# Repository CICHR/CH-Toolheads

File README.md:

CICHR Toolheads

The changeable toolheads are designed for maximum versatility and seamless integration, communicating directly with the printer via a custom PCB. This PCB enables precise control and coordination between the tool head and the printer, ensuring fast, accurate swaps between different functions. The custom PCB features:

    Heater and High-Power Outputs:
    Two high-power outputs for heaters or PWM-controlled devices with demanding power requirements.

    Temperature Sensing:
    Two thermistor inputs for accurate real-time temperature monitoring.

    PWM Outputs:
    Two PWM outputs for controlling servos, BLTouch sensors, or cooling fans.

    Digital Interfaces:
    One digital input and one digital output for additional functionality, such as endstops or status signaling.

    Stepper Motor Control:
    A dedicated output for driving a single stepper motor, ideal for toolhead-mounted extrusion or positioning tasks.

    Streamlined Communication:
    Ensures reliable communication between the toolhead and the machine, simplifying toolhead management and enhancing modularity.

This system allows you to quickly swap between different toolheads, such as 3D printing extruders, CNC milling tools, lasers, or liquid extruders, without complex rewiring, while maintaining full control over key functions.

Visit our website at www.cichr.com or https://grabcad.com/cichr-1 to learn more about our products, projects, and innovations.

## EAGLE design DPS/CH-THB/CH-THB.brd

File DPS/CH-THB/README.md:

CH-THB: The Versatile Toolhead PCB

The CH-THB is a specialized PCB board designed to manage and control a single toolhead, seamlessly connecting it to the main machine control system. This board is highly versatile, supporting various toolhead types, including 3D printers, lasers, routers, and more.

  Key Features:

      Heater and High-Power Outputs:
        Two high-power outputs for heaters or PWM-controlled devices with demanding power requirements.
      Temperature Sensing:
        Two thermistor inputs for accurate real-time temperature monitoring.
      PWM Outputs:
        Two PWM outputs for controlling servos, BLTouch sensors, or cooling fans.
      Digital Interfaces:
        One digital input and one digital output for additional functionality, such as endstops or status signaling.
      Stepper Motor Control:
        A dedicated output for driving a single stepper motor, ideal for toolhead-mounted extrusion or positioning tasks.
      Streamlined Communication:
        Ensures reliable communication between the toolhead and the machine, simplifying toolhead management and enhancing modularity.

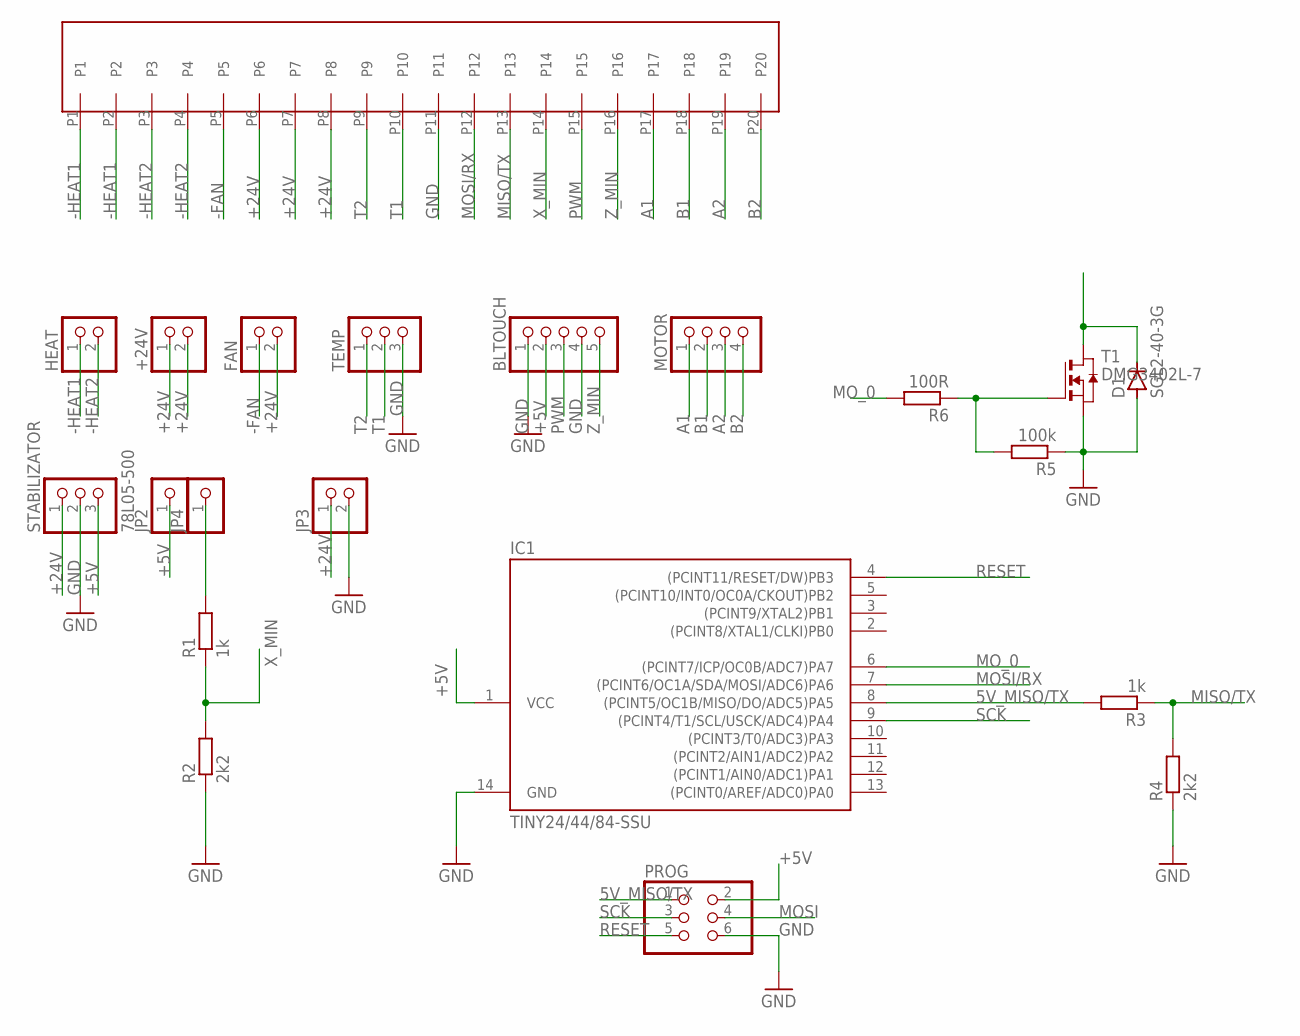
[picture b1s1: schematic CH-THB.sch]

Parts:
+24V: PINHD-1X2/LONG; 1X02
BLTOUCH: PINHD-1X5/LONG; 1X05
D1: SGL2-40-3G; SOD80
FAN: PINHD-1X2/LONG; 1X02
HEAT: PINHD-1X2/LONG; 1X02
IC1: TINY24/44/84-SSU; SOIC14
JP2, JP4: PINHD-1X1/OCT; 1X01/OCT
JP3: PINHD-1X2/OCT; 1X02/OCT
MOTOR: PINHD-1X4/LONG; 1X04
PROG: PINHD-2X3/OCT; 2X03
R1, R3: 1k; R0603
R2, R4: 2k2; R0603
R5: 100k; R0603
R6: 100R; R0603
STABILIZATOR: 78L05-500; 1X03/OCT
T1: DMG3402L-7; SOT-23
TEMP: PINHD-1X3/OCT; 1X03/OCT
U$1: PL20

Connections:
5V_MISO/TX: IC1.8 ((PCINT5/OC1B/MISO/DO/ADC5)PA5), PROG.1, R3.2
+5V: BLTOUCH.2, IC1.1 (VCC), JP2.1, PROG.2, STABILIZATOR.3
+24V: +24V.1, +24V.2, FAN.2, JP3.1, STABILIZATOR.1, U$1.P6, U$1.P7, U$1.P8
-FAN: FAN.1, U$1.P5
-HEAT1: HEAT.1, U$1.P1, U$1.P2
-HEAT2: HEAT.2, U$1.P3, U$1.P4
A1: MOTOR.1, U$1.P17
A2: MOTOR.3, U$1.P19
B1: MOTOR.2, U$1.P18
B2: MOTOR.4, U$1.P20
GND: BLTOUCH.1, BLTOUCH.4, D1.2 (A), IC1.14 (GND), JP3.2, PROG.6, R2.1, R4.1, R5.1, STABILIZATOR.2, T1.2 (S), TEMP.3, U$1.P11
MISO/TX: R3.1, R4.2, U$1.P13
MOSI: PROG.4
MOSI/RX: IC1.7 ((PCINT6/OC1A/SDA/MOSI/ADC6)PA6), U$1.P12
MO_0: IC1.6 ((PCINT7/ICP/OC0B/ADC7)PA7), R6.2
unnamed: JP4.1, R1.2
unnamed: R5.2, R6.1, T1.3 (G)
unnamed: D1.1 (C), T1.1 (D)
PWM: BLTOUCH.3, U$1.P15
RESET: IC1.4 ((PCINT11/RESET/DW)PB3), PROG.5
SCK: IC1.9 ((PCINT4/T1/SCL/USCK/ADC4)PA4), PROG.3
T1: TEMP.2, U$1.P10
T2: TEMP.1, U$1.P9
X_MIN: R1.1, R2.2, U$1.P14
Z_MIN: BLTOUCH.5, U$1.P16

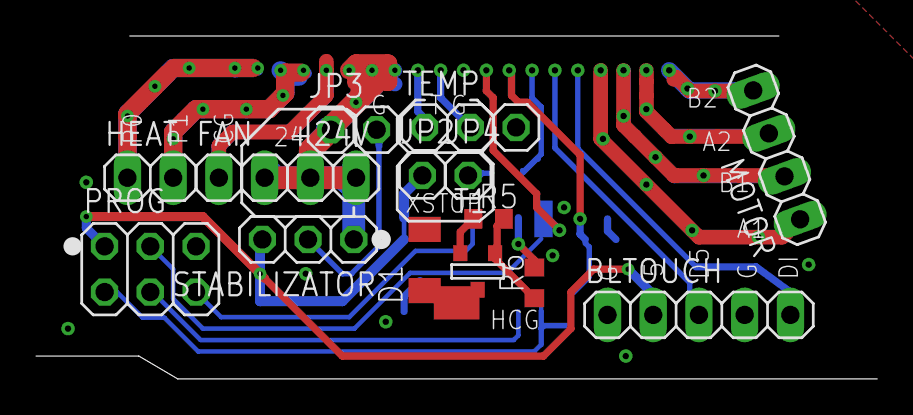
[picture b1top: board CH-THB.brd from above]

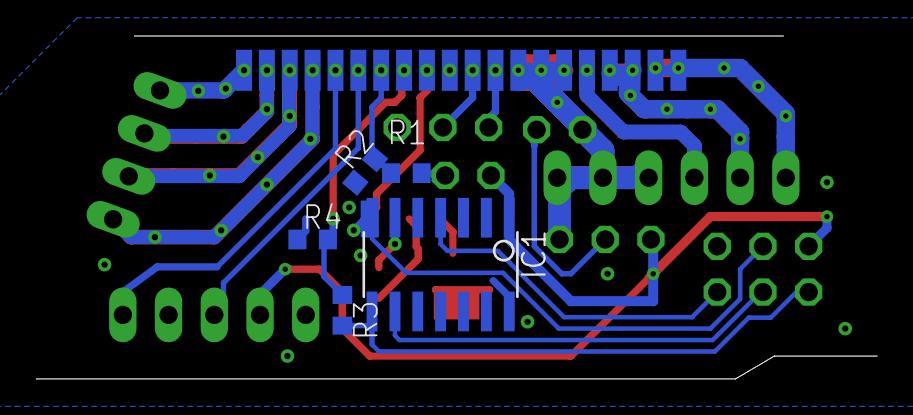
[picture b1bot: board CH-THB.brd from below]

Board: 2 copper layers, 46.7 x 19.0 mm, 21 parts (6 on the bottom side), 24 nets.

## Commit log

2024-12-05 Create STEP
2024-12-05 Rename READEME.md to README.md
2024-12-16 Create FFF
